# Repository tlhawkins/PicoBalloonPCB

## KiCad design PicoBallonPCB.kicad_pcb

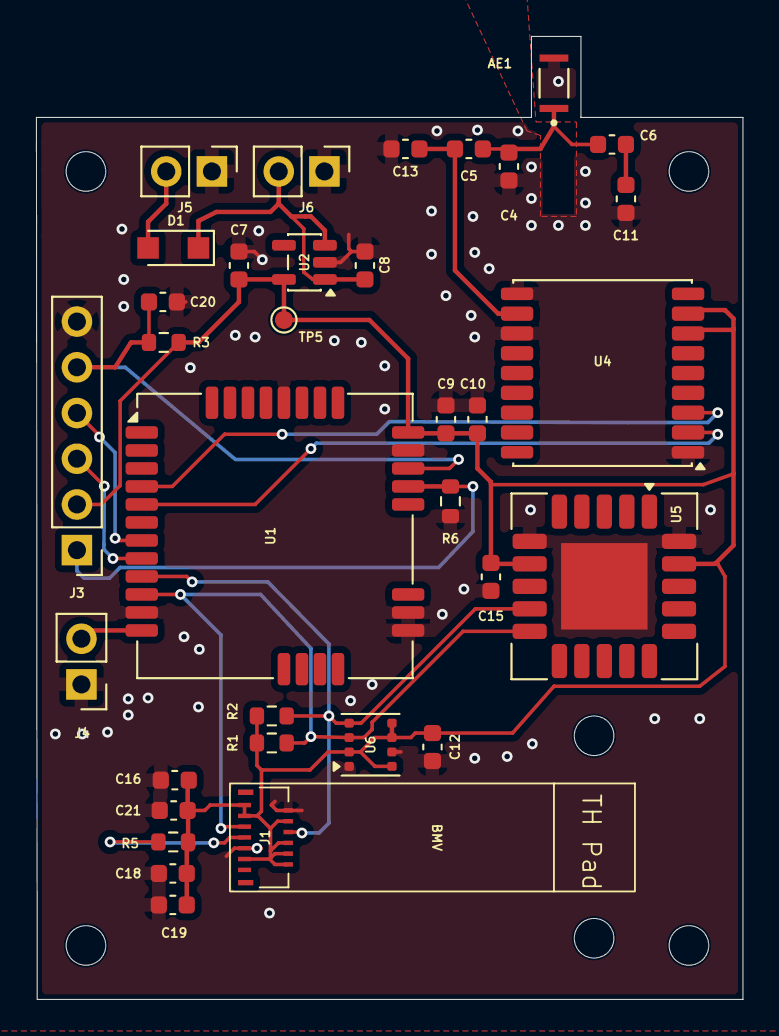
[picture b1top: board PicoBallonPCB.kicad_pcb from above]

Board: 2 copper layers, 39.2 x 53.5 mm, 41 parts (0 on the bottom side), 17 nets.

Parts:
AE1: GGBLA.01.A; XCVR_GGBLA.01.A
BMV: BMV080
C4: 0.8pF; C_0603_1608Metric
C5: 2.7pF; C_0603_1608Metric
C6: 0.5pF; C_0603_1608Metric
C7, C8: 1uF; C_0603_1608Metric
C9: 10uF; C_0603_1608Metric
C10, C12, C15, C20: 100nF; C_0603_1608Metric
C11: 22pF; C_0603_1608Metric
C13: DNF; C_0603_1608Metric
C16, C18, C19, C21: 2.2uF; C_0603_1608Metric
D1: MBR0560-TP; Nexperia_CFP3_SOD-123W
H1: MountingHole_PadBMV1; MountingHole_2.2mm_M2
H2: MountingHole_PadBMV2; MountingHole_2.2mm_M2
H3, H4, H5, H6: MountingHole_PadCorner; MountingHole_2.2mm_M2
J1: 503566-1302; 5035661302
J3: RF; PinHeader_1x02_P2.54mm_Vertical
J4: SWD; PinHeader_1x06_P2.54mm_Vertical
J5: Sol Pwr; PinHeader_1x02_P2.54mm_Vertical
J6: Caps; PinHeader_1x02_P2.54mm_Vertical
R1, R2: 4.7k; R_0603_1608Metric
R3, R5, R6: 10k; R_0603_1608Metric
TP5: 3.3V; TestPoint_Pad_D1.0mm
U1: RAK3172
U2: TLV70025_SOT23-5; SOT-23-5
U4: MAX-M10S; ublox_MAX
U5: SCD41-D-R2; Sensirion_SCD4x-1EP_10.1x10.1mm_P1.25mm_EP4.8x4.8mm
U6: BME680; Bosch_LGA-8_3x3mm_P0.8mm_ClockwisePinNumbering

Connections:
+3.3V: C7.1, C9.1, C10.1, C12.1, C15.1, C16.1, C18.1, C19.1, C21.1, J1.1 (VDDL), J1.3 (VDDA), J1.4 (CSB), J1.8 (VDDIO), J1.10 (VDDD), J1.11 (MISO/IAB0), J1.12 (IRQ), J4.2, R1.1, R2.1, R3.1, R5.1, TP5.1 (1_1), U1.24 (VDD), U2.5 (OUT), U4.7 (VCC_IO), U4.8 (VCC), U5.7 (VDD), U5.19 (VDD), U6.2 (CSB), U6.5 (SDO), U6.6 (VDDIO), U6.8 (VDD)
+BATT: D1.2 (A), J5.2
BOOT0: J4.1, R6.1, U1.21 (BOOT0)
C+: C8.1, D1.1 (K), J6.2, U2.1 (IN), U2.3 (EN)
GND: AE1.2 (Gnd_2), C4.2, C7.2, C8.2, C9.2, C10.2, C11.2, C12.2, C13.2, C15.2, C16.2, C18.2, C19.2, C20.2, C21.2, J1.2 (VSSA), J1.9 (VSSD), J3.1, J4.6, J5.1, J6.1, R6.2, U1.11 (GND), U1.17 (GND), U1.18 (GND), U1.23 (GND), U1.28 (GND), U2.2 (GND), U4.1 (GND), U4.10 (GND), U4.12 (GND), U5.6 (GND), U5.20 (GND), U5.21 (GND), U6.1 (GND), U6.7 (GND)
GPSRX: U1.5 (PB7/UART1_RX), U4.2 (TXD)
GPSTX: U1.4 (PB6/UART1_TX), U4.3 (RXD)
unnamed: C6.2, C11.1
unnamed: AE1.1, C4.1, C5.2, C6.1
unnamed: J1.7 (PS), R5.2
unnamed: C5.1, C13.1, U4.11 (RF_IN)
RESET: C20.1, J4.5, R3.2, U1.22 (~RST)
RF: J3.2, U1.12 (RF)
SCL: J1.6 (SCL), R2.2, U1.9 (PA12/I2C_SCL), U5.9 (SCL), U6.4 (SCK)
SDA: J1.5 (MOSI/SDA), R1.2, U1.10 (PA11/I2C_SDA), U5.10 (SDA), U6.3 (SDI)
SWCLK: J4.3, U1.8 (PA14/SWCLK)
SWDIO: J4.4, U1.7 (PA13/SWDIO)

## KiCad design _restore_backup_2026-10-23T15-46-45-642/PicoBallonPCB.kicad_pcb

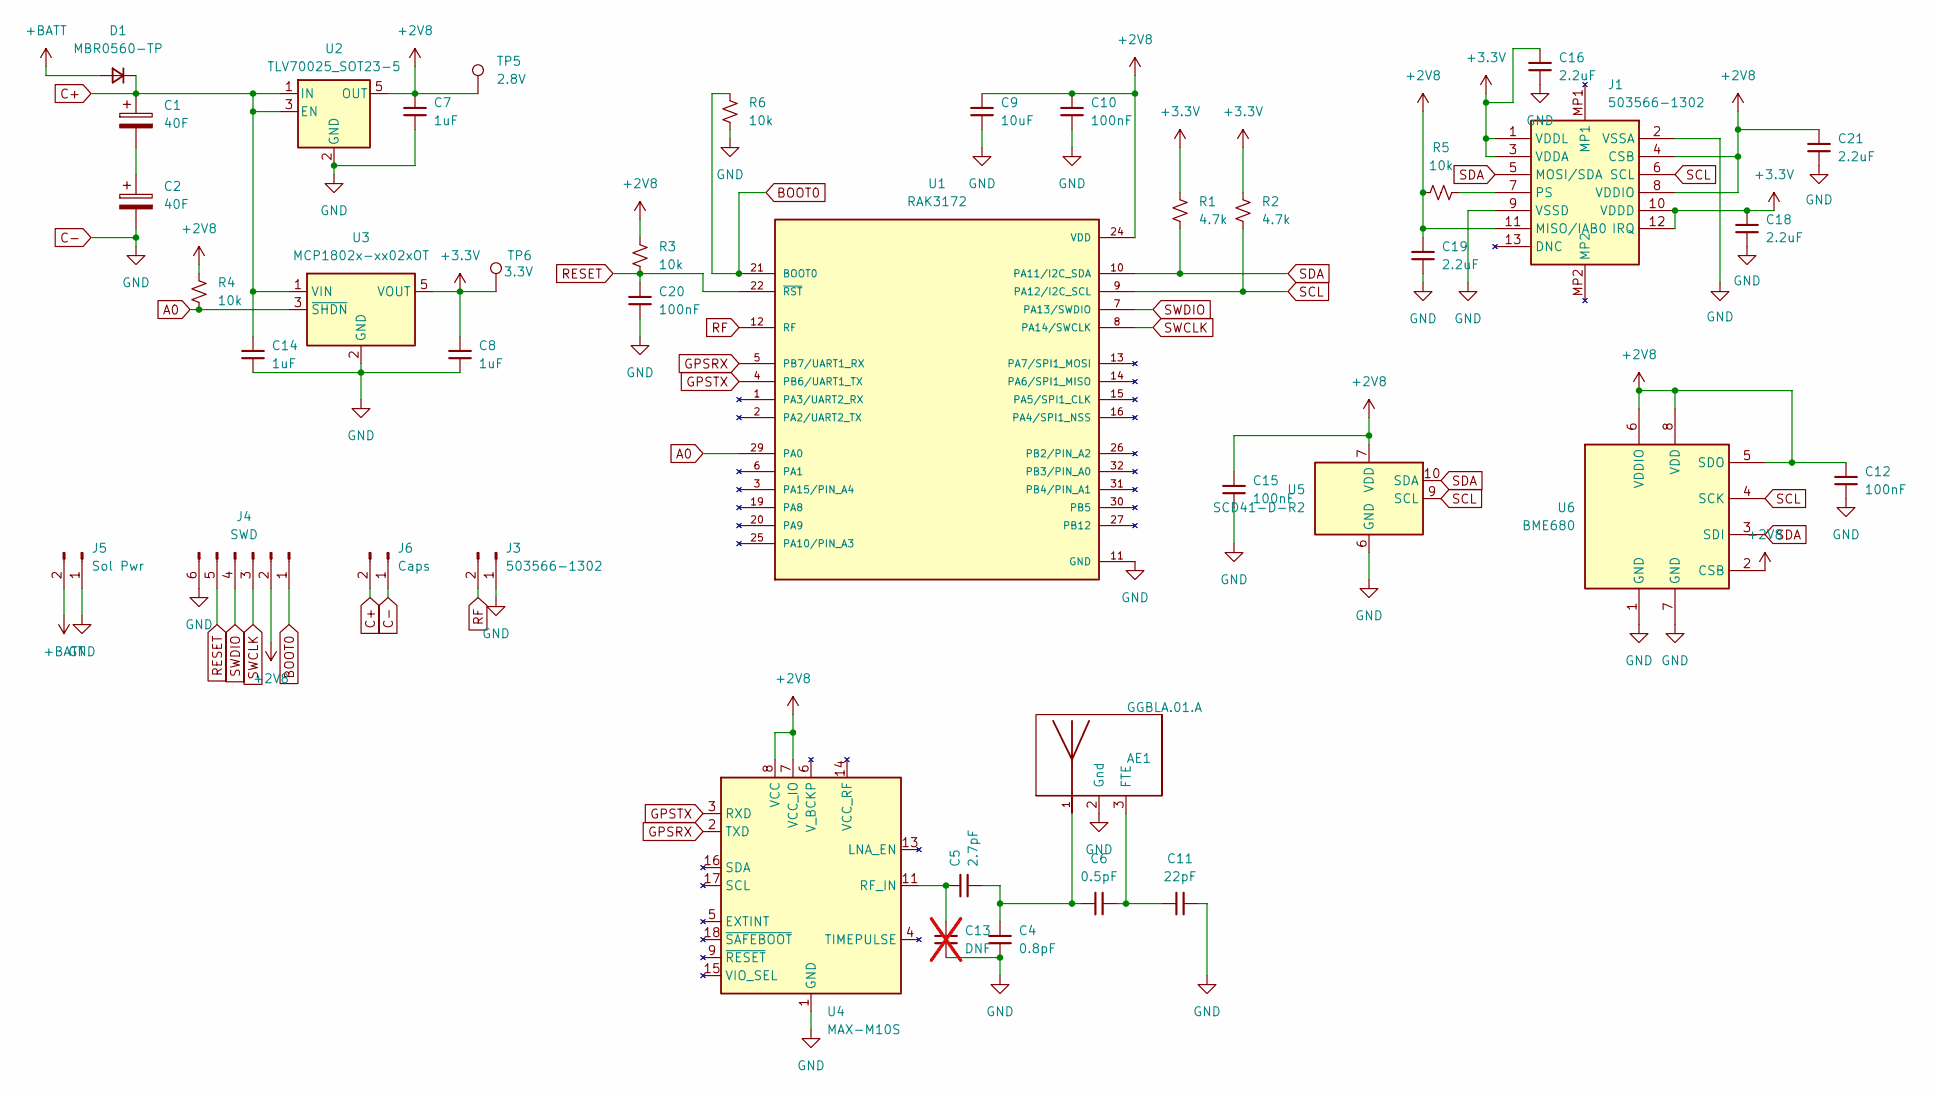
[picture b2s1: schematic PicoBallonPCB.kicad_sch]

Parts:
AE1: GGBLA.01.A; XCVR_GGBLA.01.A; PARTREV SPE-13-8-092/H/PK
C1, C2: 40F; Texas_DSG0008A_WSON-8-1EP_2x2mm_P0.5mm_EP0.9x1.6mm
C4: 0.8pF; C_0603_1608Metric
C5: 2.7pF; C_0603_1608Metric
C6: 0.5pF; C_0603_1608Metric
C7, C8, C14: 1uF; C_0603_1608Metric
C9: 10uF; C_0603_1608Metric
C10, C12, C15, C20: 100nF; C_0603_1608Metric
C11: 22pF; C_0603_1608Metric
C13: DNF; C_0603_1608Metric; not fitted
C16, C18, C19, C21: 2.2uF; C_0603_1608Metric
D1: MBR0560-TP; Nexperia_CFP3_SOD-123W
J1: 503566-1302; 5035661302; Mouser Part Number 538-503566-1302
J3: 503566-1302; PinHeader_1x02_P2.54mm_Vertical
J4: SWD; PinHeader_1x06_P2.54mm_Vertical
J5: Sol Pwr; PinHeader_1x02_P2.54mm_Vertical
J6: Caps; PinHeader_1x02_P2.54mm_Vertical
R1, R2: 4.7k; C_0603_1608Metric
R3, R4, R5, R6: 10k; C_0603_1608Metric
TP5: 2.8V; C_0603_1608Metric
TP6: 3.3V; C_0603_1608Metric
U1: RAK3172; PARTREV 20/02/2026
U2: TLV70025_SOT23-5; SOT-23-5
U3: MCP1802x-xx02xOT; SOT-23-5
U4: MAX-M10S; ublox_MAX
U5: SCD41-D-R2; Sensirion_SCD4x-1EP_10.1x10.1mm_P1.25mm_EP4.8x4.8mm
U6: BME680; Bosch_LGA-8_3x3mm_P0.8mm_ClockwisePinNumbering

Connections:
+2V8: C7.1, C9.1, C10.1, C12.1, C15.1, C19.1, C21.1, J1.4 (CSB), J1.8 (VDDIO), J1.11 (MISO/IAB0), J4.2, R3.1, R4.1, R5.1, TP5.1 (1_1), U1.24 (VDD), U2.5 (OUT), U4.7 (VCC_IO), U4.8 (VCC), U5.7 (VDD), U5.19 (VDD), U6.2 (CSB), U6.5 (SDO), U6.6 (VDDIO), U6.8 (VDD)
+3.3V: C8.1, C16.1, C18.1, J1.1 (VDDL), J1.3 (VDDA), J1.10 (VDDD), J1.12 (IRQ), R1.1, R2.1, TP6.1 (1_1), U3.5 (VOUT)
+BATT: D1.2 (A), J5.2
A0: R4.2, U1.29 (PA0), U3.3 (~SHDN)
BOOT0: J4.1, R6.1, U1.21 (BOOT0)
C+: C1.1, C14.1, D1.1 (K), J6.2, U2.1 (IN), U2.3 (EN), U3.1 (VIN)
C-: AE1.2 (Gnd), C2.2, C4.2, C7.2, C8.2, C9.2, C10.2, C11.2, C12.2, C13.2, C14.2, C15.2, C16.2, C18.2, C19.2, C20.2, C21.2, J1.2 (VSSA), J1.9 (VSSD), J3.1, J4.6, J5.1, J6.1, R6.2, U1.11 (GND), U1.17 (GND), U1.18 (GND), U1.23 (GND), U1.28 (GND), U2.2 (GND), U3.2 (GND), U4.1 (GND), U4.10 (GND), U4.12 (GND), U5.6 (GND), U5.20 (GND), U5.21 (GND), U6.1 (GND), U6.7 (GND)
GPSRX: U1.5 (PB7/UART1_RX), U4.2 (TXD)
GPSTX: U1.4 (PB6/UART1_TX), U4.3 (RXD)
unnamed: AE1.3 (FTE), C6.2, C11.1
unnamed: AE1.1, C4.1, C5.2, C6.1
unnamed: C1.2, C2.1
unnamed: J1.7 (PS), R5.2
unnamed: C5.1, C13.1, U4.11 (RF_IN)
RESET: C20.1, J4.5, R3.2, U1.22 (~RST)
RF: J3.2, U1.12 (RF)
SCL: J1.6 (SCL), R2.2, U1.9 (PA12/I2C_SCL), U5.9 (SCL), U6.4 (SCK)
SDA: J1.5 (MOSI/SDA), R1.2, U1.10 (PA11/I2C_SDA), U5.10 (SDA), U6.3 (SDI)
SWCLK: J4.3, U1.8 (PA14/SWCLK)
SWDIO: J4.4, U1.7 (PA13/SWDIO)

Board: 4 copper layers, 36 parts (0 on the bottom side), 14 nets, no tracks yet.
